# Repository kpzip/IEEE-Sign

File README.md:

# IEEE Sign

It's a sign that says "IEEE" using Argb lights. I don't know what more to say.

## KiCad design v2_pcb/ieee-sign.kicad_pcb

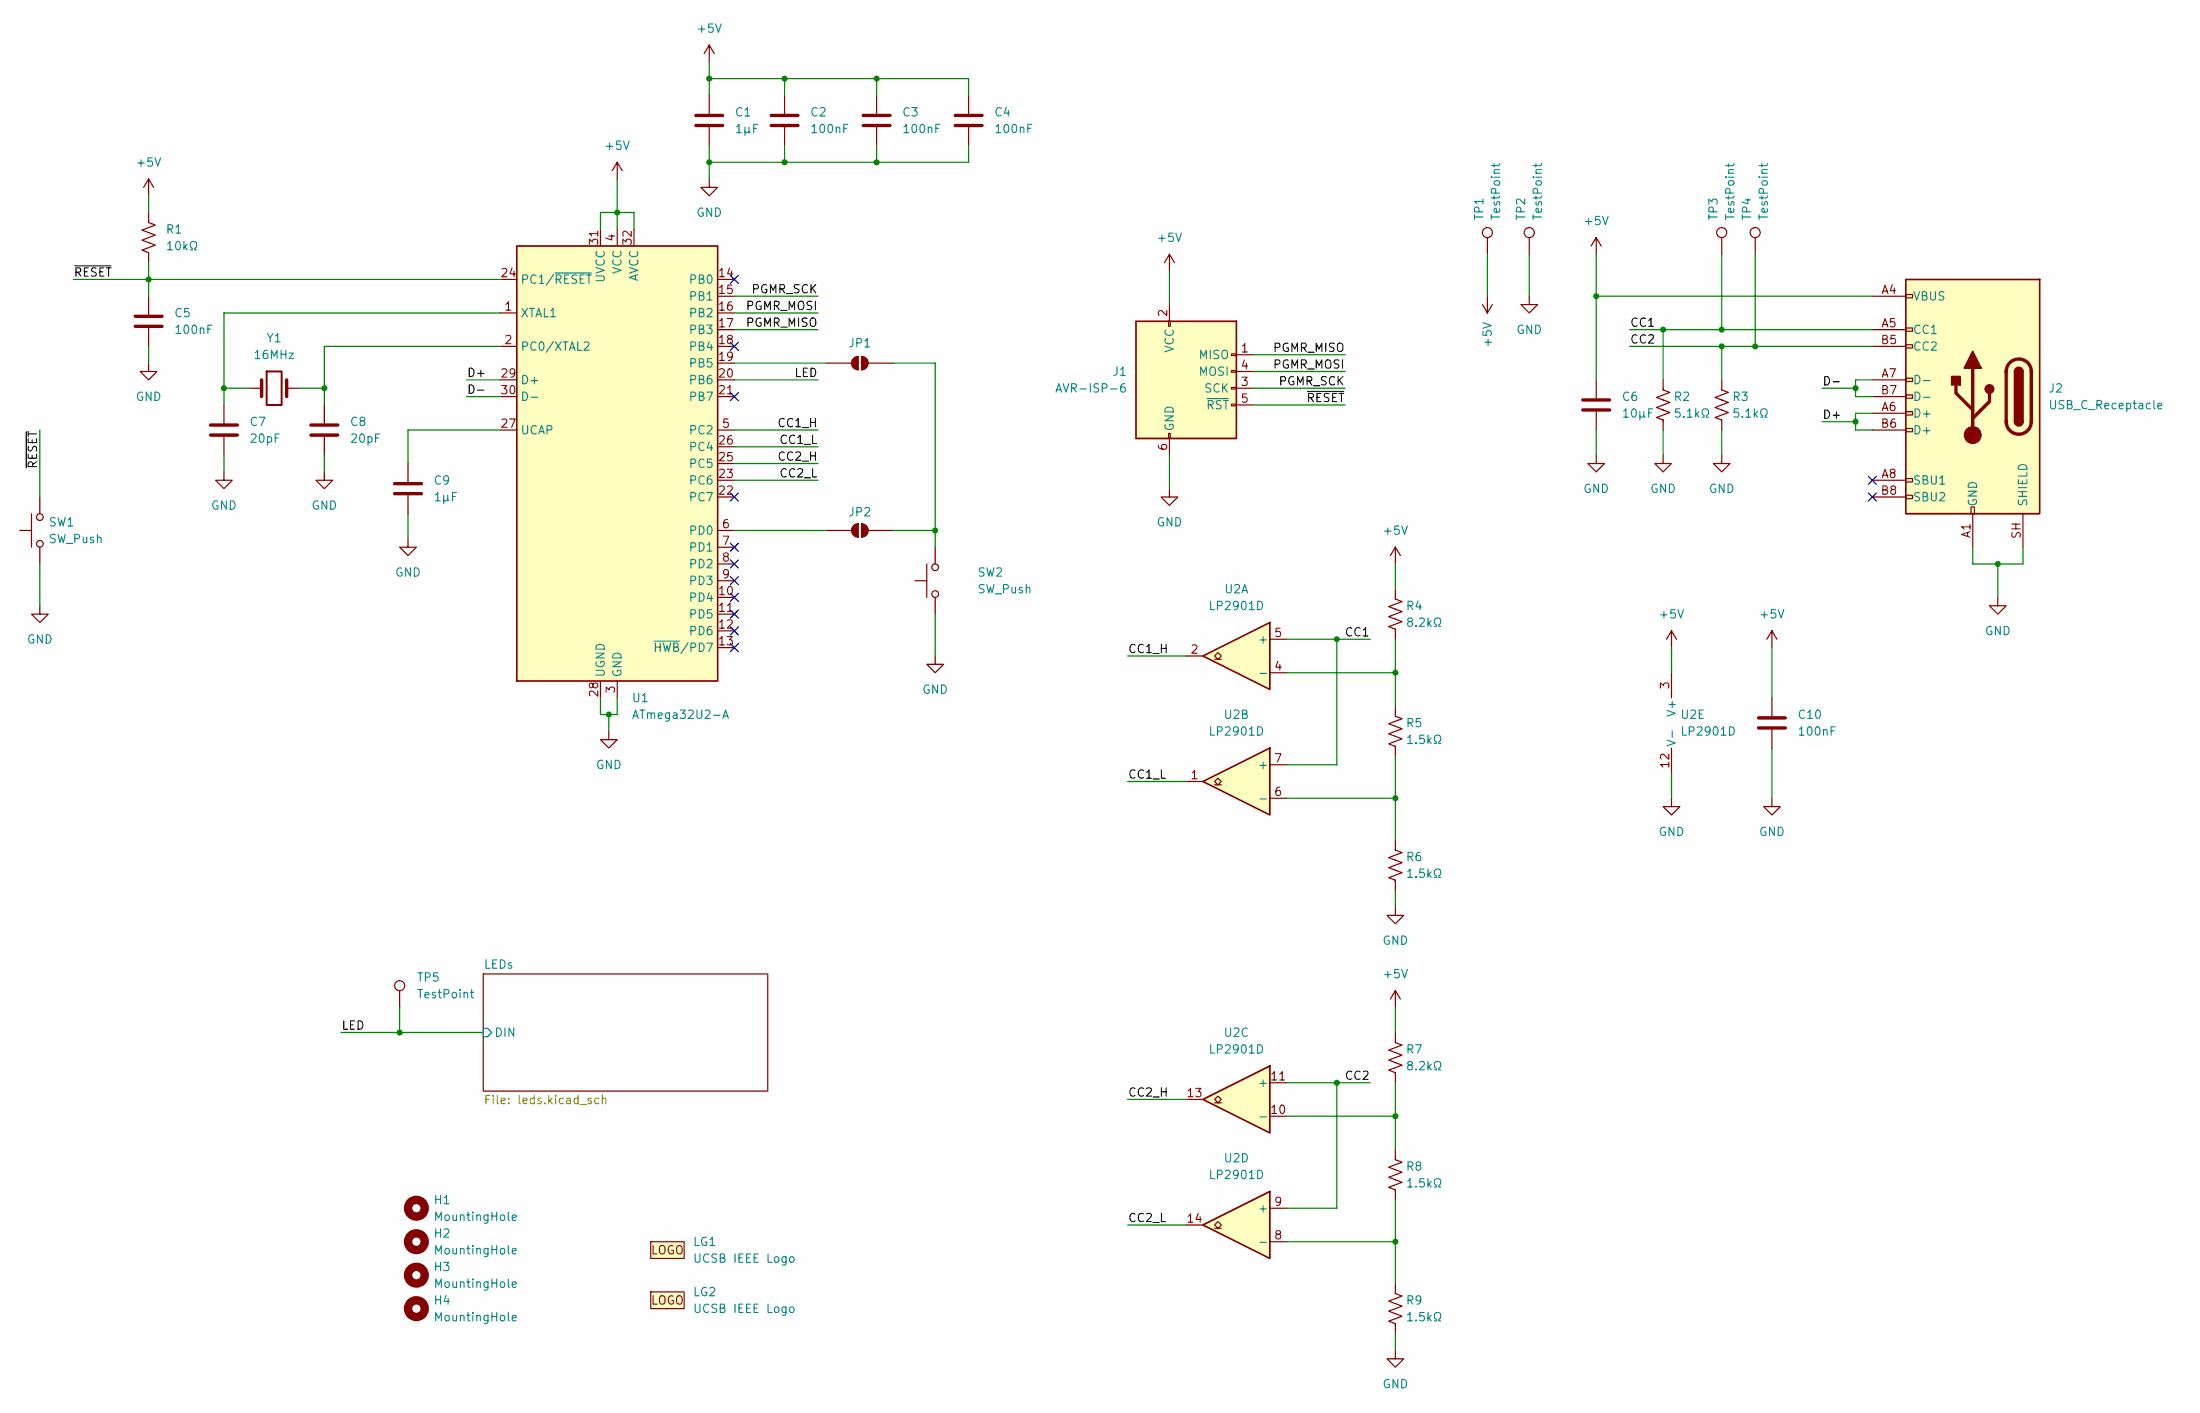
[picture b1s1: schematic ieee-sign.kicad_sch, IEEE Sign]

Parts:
C1, C9: 1μF; C_1206_3216Metric_Pad1.33x1.80mm_HandSolder; Manufacturer Part Number CL31B105KAHNNNE
C2, C3, C4, C5, C10: 100nF; C_1206_3216Metric_Pad1.33x1.80mm_HandSolder; Manufacturer Part Number C1206C104K5RACTU
C6: 10μF; C_1206_3216Metric_Pad1.33x1.80mm_HandSolder; Manufacturer Part Number CL31A106MAHNNNE
C7, C8: 20pF; C_0603_1608Metric_Pad1.08x0.95mm_HandSolder; Manufacturer Part Number C0603C200J5GACTU
H1, H2, H3, H4: MountingHole; MountingHole_3.2mm_M3
J1: AVR-ISP-6; IDC-Header_2x03_P2.54mm_Vertical; Manufacturer Part Number 61200621621
J2: USB_C_Receptacle; USB_C_Receptacle_GCT_USB4105-xx-A_16P_TopMnt_Horizontal; Manufacturer Part Number USB4105-GF-A
JP1, JP2: SolderJumper-2_P1.3mm_Open_RoundedPad1.0x1.5mm
LG1: UCSB IEEE Logo; UCSB_IEEE_Logo
LG2: UCSB IEEE Logo; UCSB_IEEE_Logo_Text
R1: 10kΩ; R_1206_3216Metric_Pad1.30x1.75mm_HandSolder; Manufacturer Part Number RMCF1206FT10K0
R2, R3: 5.1kΩ; R_1206_3216Metric_Pad1.30x1.75mm_HandSolder; Manufacturer Part Number RC1206FR-075K1L
R4, R7: 8.2kΩ; R_1206_3216Metric_Pad1.30x1.75mm_HandSolder; Manufacturer Part Number RC1206FR-078K2L
R5, R6, R8, R9: 1.5kΩ; R_1206_3216Metric_Pad1.30x1.75mm_HandSolder; Manufacturer Part Number RNCP1206FTD1K50
SW1, SW2: SW_Push; SW_PUSH_6mm; Manufacturer Part Number PTS645SL43-2 LFS
TP1, TP2, TP3, TP4, TP5: TestPoint; TestPoint_Pad_D1.0mm
U1: ATmega32U2-A; TQFP-32_7x7mm_P0.8mm; Manufacturer Part Number ATMEGA32U2-AUR
U2: LP2901D; SOIC-14_3.9x8.7mm_P1.27mm; Manufacturer Part Number LP2901D
Y1: 16MHz; Crystal_HC49-U_Vertical; Manufacturer Part Number 16M20P2/49US

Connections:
+5V: C1.1, C2.1, C3.1, C4.1, C6.1, C10.1, J1.2 (VCC), J2.A4 (VBUS), J2.A9 (VBUS), J2.B4 (VBUS), J2.B9 (VBUS), R1.1, R4.1, R7.1, TP1.1 (1_1), U1.4 (VCC), U1.31 (UVCC), U1.32 (AVCC), U2.3 (V+); also elsewhere on the board
/CC1: J2.A5 (CC1), R2.1, TP3.1 (1_1), U2.5 (+), U2.7 (+)
/CC1_H: U1.5 (PC2), U2.2
/CC1_L: U1.26 (PC4), U2.1
/CC2: J2.B5 (CC2), R3.1, TP4.1 (1_1), U2.9 (+), U2.11 (+)
/CC2_H: U1.25 (PC5), U2.13
/CC2_L: U1.23 (PC6), U2.14
/D+: J2.A6 (D+), J2.B6 (D+), U1.29 (D+)
/D-: J2.A7 (D-), J2.B7 (D-), U1.30 (D-)
/LED: TP5.1 (1_1), U1.20 (PB6); also elsewhere on the board
/PGMR_MISO: J1.1 (MISO), U1.17 (PB3)
/PGMR_MOSI: J1.4 (MOSI), U1.16 (PB2)
/PGMR_SCK: J1.3 (SCK), U1.15 (PB1)
/~RESET: C5.1, J1.5 (~RST), R1.2, SW1.2, U1.24 (PC1/~RESET)
GND: C1.2, C2.2, C3.2, C4.2, C5.2, C6.2, C7.2, C8.2, C9.2, C10.2, J1.6 (GND), J2.A1 (GND), J2.A12 (GND), J2.B1 (GND), J2.B12 (GND), J2.SH (SHIELD), R2.2, R3.2, R6.2, R9.2, SW1.1, SW2.1, TP2.1 (1_1), U1.3 (GND), U1.28 (UGND), U2.12 (V-); also elsewhere on the board
unnamed: JP1.1 (A), U1.19 (PB5)
unnamed: JP1.2 (B), JP2.2 (B), SW2.2
unnamed: JP2.1 (A), U1.6 (PD0)
unnamed: C8.1, U1.2 (PC0/XTAL2), Y1.2
unnamed: C9.1, U1.27 (UCAP)
unnamed: C7.1, U1.1 (XTAL1), Y1.1
unnamed: R4.2, R5.1, U2.4 (-)
unnamed: R5.2, R6.1, U2.6 (-)
unnamed: R7.2, R8.1, U2.10 (-)
unnamed: R8.2, R9.1, U2.8 (-)

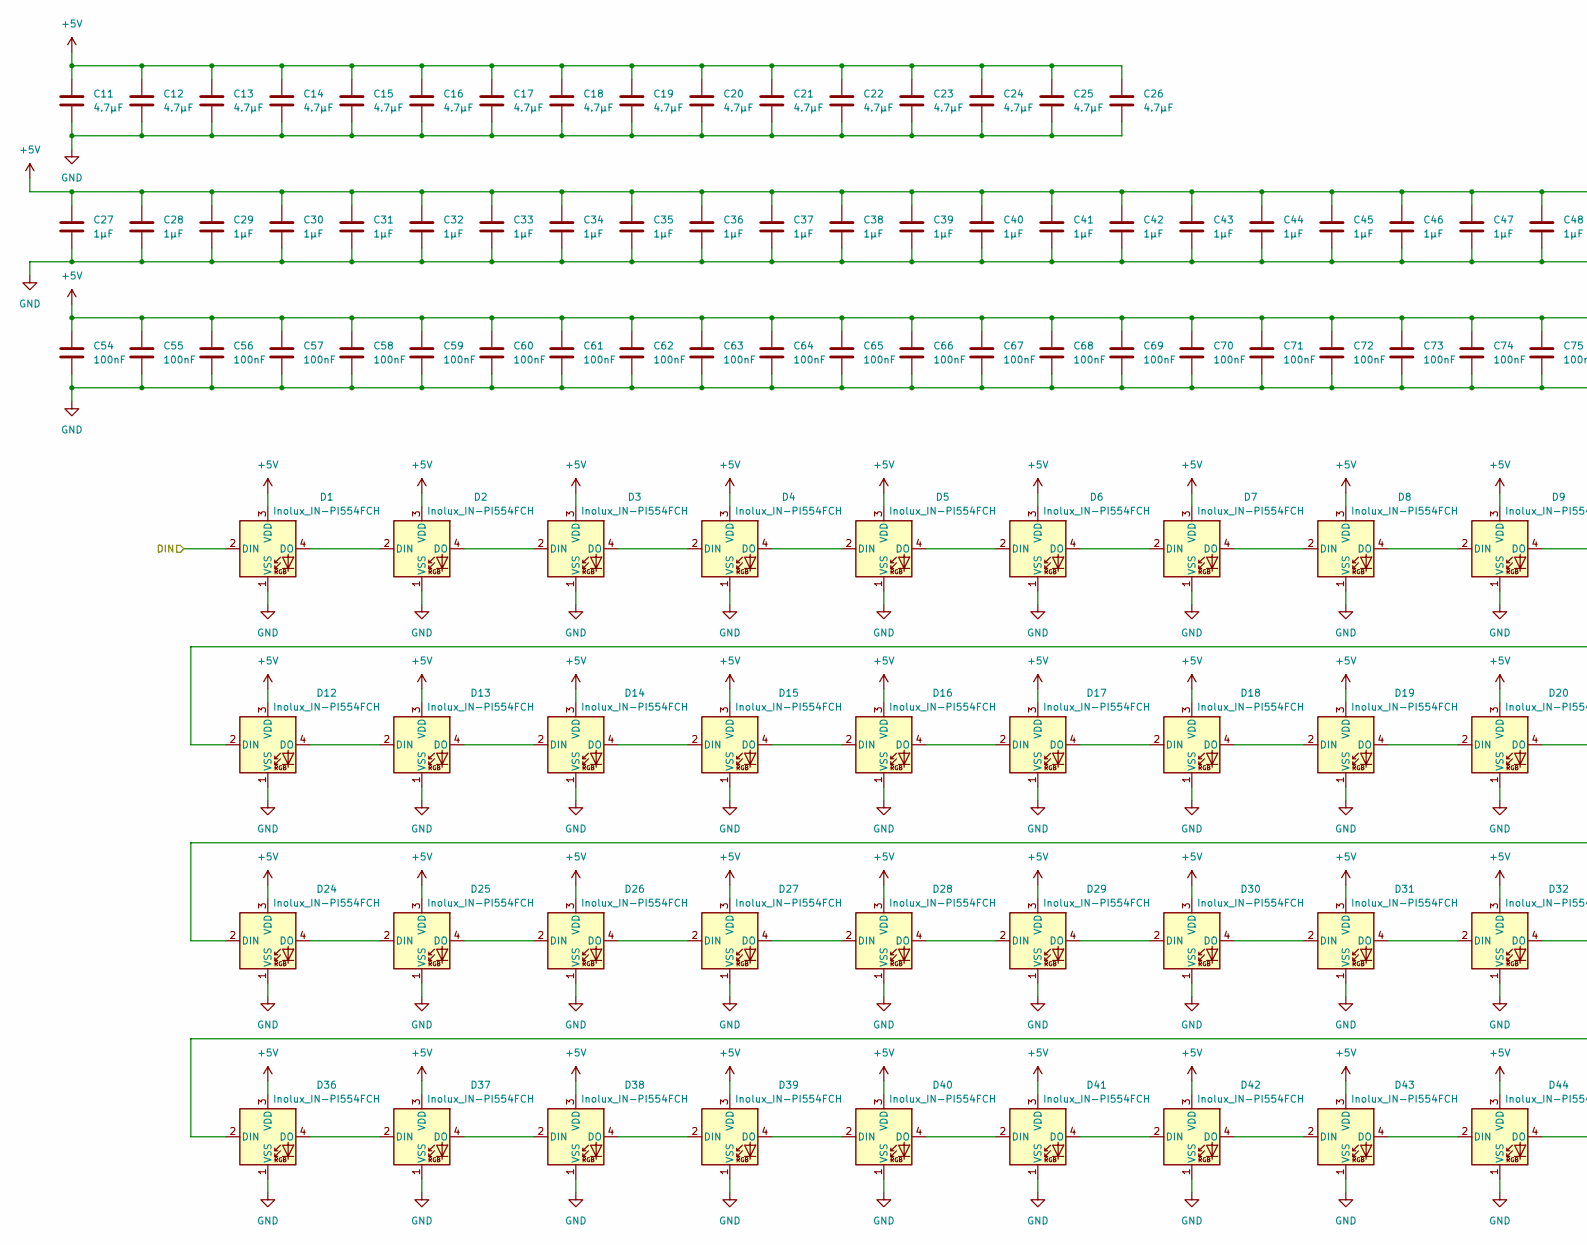
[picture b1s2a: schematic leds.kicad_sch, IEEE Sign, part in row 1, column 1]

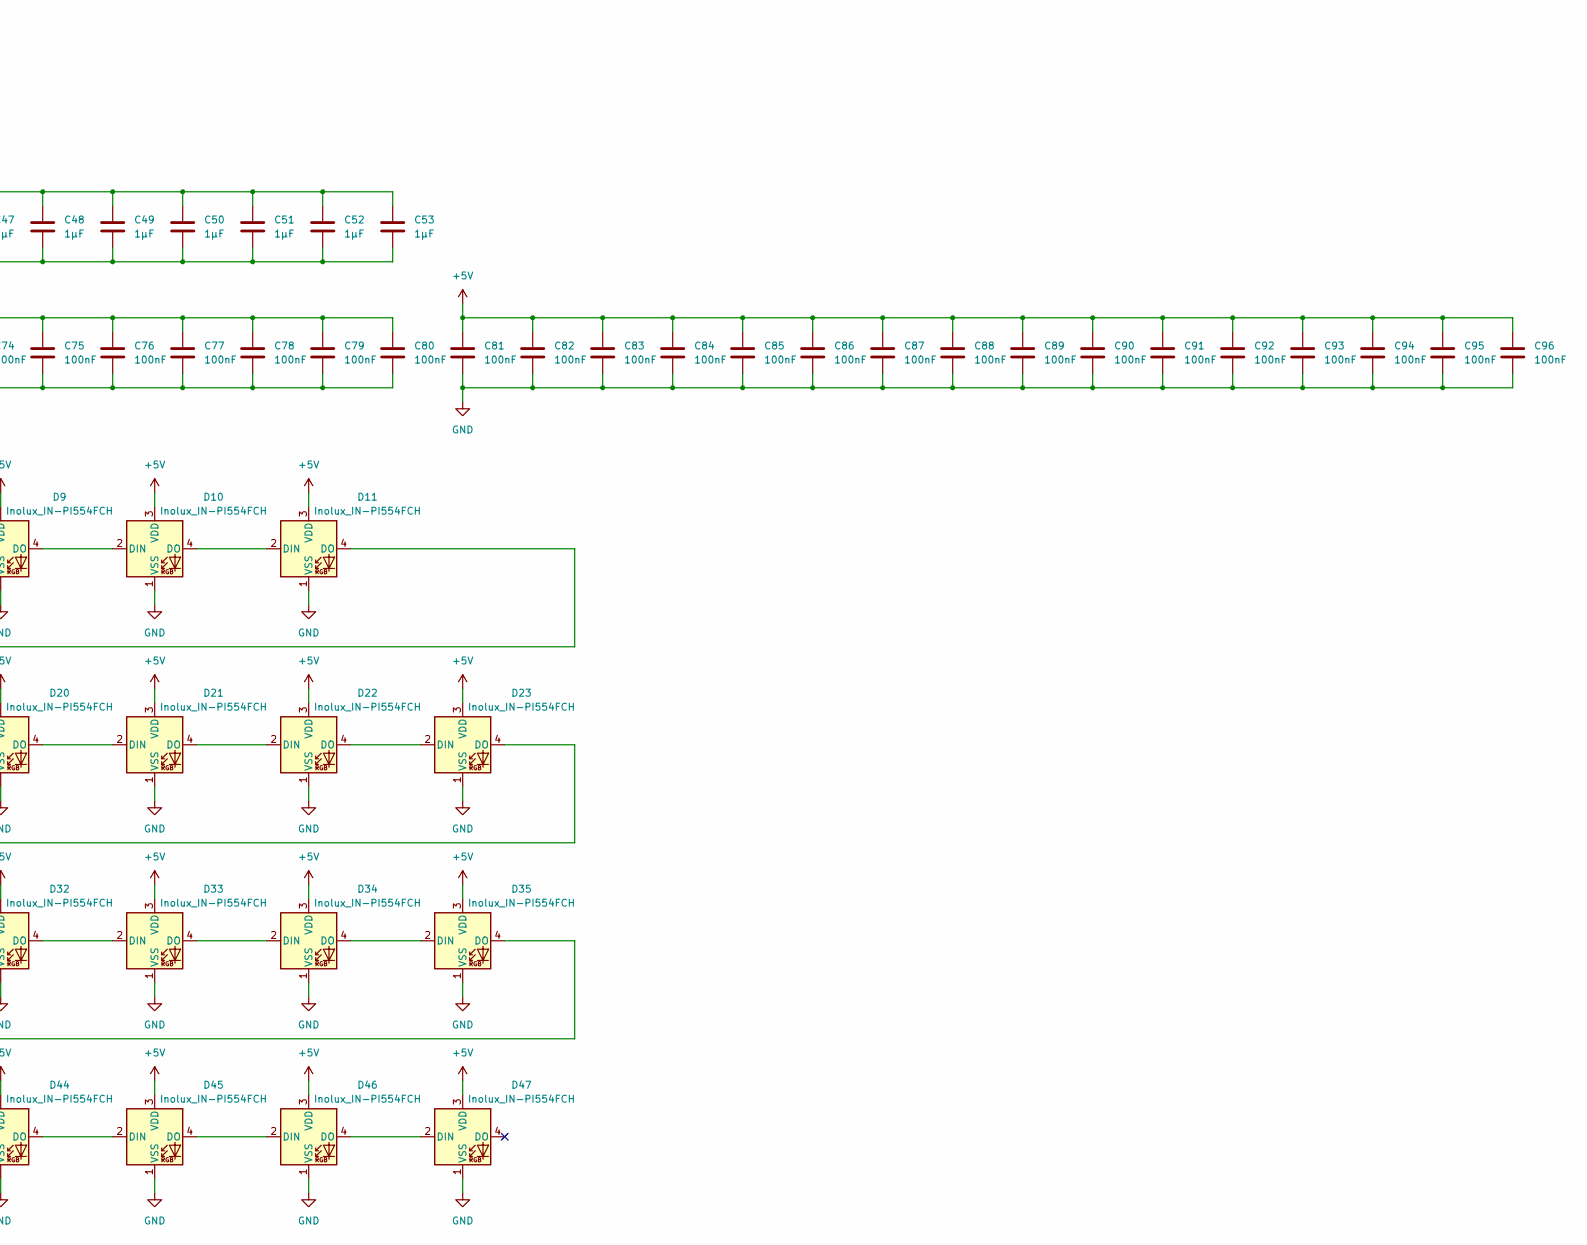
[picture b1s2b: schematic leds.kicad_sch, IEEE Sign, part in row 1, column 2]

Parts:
C11, C12, C13, C14, C15, C16, C17, C18, C19, C20, C21, C22, C23, C24, C25, C26: 4.7μF; C_1206_3216Metric_Pad1.33x1.80mm_HandSolder; Manufacturer Part Number CL31B475KAHNNNE
C27, C28, C29, C30, C31, C32, C33, C34, C35, C36, C37, C38, C39, C40, C41, C42, C43, C44, C45, C46, C47, C48, C49, C50, C51, C52, C53: 1μF; C_1206_3216Metric_Pad1.33x1.80mm_HandSolder; Manufacturer Part Number CL31B105KAHNNNE
C54, C55, C56, C57, C58, C59, C60, C61, C62, C63, C64, C65, C66, C67, C68, C69, C70, C71, C72, C73, C74, C75, C76, C77, C78, C79, C80, C81, C82, C83, C84, C85, C86, C87, C88, C89, C90, C91, C92, C93, C94, C95, C96: 100nF; C_1206_3216Metric_Pad1.33x1.80mm_HandSolder; Manufacturer Part Number C1206C104K5RACTU
D1, D2, D3, D4, D5, D6, D7, D8, D9, D10, D11, D12, D13, D14, D15, D16, D17, D18, D19, D20, D21, D22, D23, D24, D25, D26, D27, D28, D29, D30, D31, D32, D33, D34, D35, D36, D37, D38, D39, D40, D41, D42, D43, D44, D45, D46, D47: Inolux_IN-PI554FCH; LED_Inolux_IN-PI554FCH_PLCC4_5.0x5.0mm_P3.2mm; Manufacturer Part Number IN-PI554FCH

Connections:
+5V: C11.1, C12.1, C13.1, C14.1, C15.1, C16.1, C17.1, C18.1, C19.1, C20.1, C21.1, C22.1, C23.1, C24.1, C25.1, C26.1, C27.1, C28.1, C29.1, C30.1, C31.1, C32.1, C33.1, C34.1, C35.1, C36.1, C37.1, C38.1, C39.1, C40.1, C41.1, C42.1, C43.1, C44.1, C45.1, C46.1, C47.1, C48.1, C49.1, C50.1, C51.1, C52.1, C53.1, C54.1, C55.1, C56.1, C57.1, C58.1, C59.1, C60.1, C61.1, C62.1, C63.1, C64.1, C65.1, C66.1, C67.1, C68.1, C69.1, C70.1, C71.1, C72.1, C73.1, C74.1, C75.1, C76.1, C77.1, C78.1, C79.1, C80.1, C81.1, C82.1, C83.1, C84.1, C85.1, C86.1, C87.1, C88.1, C89.1, C90.1, C91.1, C92.1, C93.1, C94.1, C95.1, C96.1, D1.3 (VDD), D2.3 (VDD), D3.3 (VDD), D4.3 (VDD), D5.3 (VDD), D6.3 (VDD), D7.3 (VDD), D8.3 (VDD), D9.3 (VDD), D10.3 (VDD), D11.3 (VDD), D12.3 (VDD), D13.3 (VDD), D14.3 (VDD), D15.3 (VDD), D16.3 (VDD), D17.3 (VDD), D18.3 (VDD), D19.3 (VDD), D20.3 (VDD), D21.3 (VDD), D22.3 (VDD), D23.3 (VDD), D24.3 (VDD), D25.3 (VDD), D26.3 (VDD), D27.3 (VDD), D28.3 (VDD), D29.3 (VDD), D30.3 (VDD), D31.3 (VDD), D32.3 (VDD), D33.3 (VDD), D34.3 (VDD), D35.3 (VDD), D36.3 (VDD), D37.3 (VDD), D38.3 (VDD), D39.3 (VDD), D40.3 (VDD), D41.3 (VDD), D42.3 (VDD), D43.3 (VDD), D44.3 (VDD), D45.3 (VDD), D46.3 (VDD), D47.3 (VDD); also elsewhere on the board
/LED: D1.2 (DIN); also elsewhere on the board
GND: C11.2, C12.2, C13.2, C14.2, C15.2, C16.2, C17.2, C18.2, C19.2, C20.2, C21.2, C22.2, C23.2, C24.2, C25.2, C26.2, C27.2, C28.2, C29.2, C30.2, C31.2, C32.2, C33.2, C34.2, C35.2, C36.2, C37.2, C38.2, C39.2, C40.2, C41.2, C42.2, C43.2, C44.2, C45.2, C46.2, C47.2, C48.2, C49.2, C50.2, C51.2, C52.2, C53.2, C54.2, C55.2, C56.2, C57.2, C58.2, C59.2, C60.2, C61.2, C62.2, C63.2, C64.2, C65.2, C66.2, C67.2, C68.2, C69.2, C70.2, C71.2, C72.2, C73.2, C74.2, C75.2, C76.2, C77.2, C78.2, C79.2, C80.2, C81.2, C82.2, C83.2, C84.2, C85.2, C86.2, C87.2, C88.2, C89.2, C90.2, C91.2, C92.2, C93.2, C94.2, C95.2, C96.2, D1.1 (VSS), D2.1 (VSS), D3.1 (VSS), D4.1 (VSS), D5.1 (VSS), D6.1 (VSS), D7.1 (VSS), D8.1 (VSS), D9.1 (VSS), D10.1 (VSS), D11.1 (VSS), D12.1 (VSS), D13.1 (VSS), D14.1 (VSS), D15.1 (VSS), D16.1 (VSS), D17.1 (VSS), D18.1 (VSS), D19.1 (VSS), D20.1 (VSS), D21.1 (VSS), D22.1 (VSS), D23.1 (VSS), D24.1 (VSS), D25.1 (VSS), D26.1 (VSS), D27.1 (VSS), D28.1 (VSS), D29.1 (VSS), D30.1 (VSS), D31.1 (VSS), D32.1 (VSS), D33.1 (VSS), D34.1 (VSS), D35.1 (VSS), D36.1 (VSS), D37.1 (VSS), D38.1 (VSS), D39.1 (VSS), D40.1 (VSS), D41.1 (VSS), D42.1 (VSS), D43.1 (VSS), D44.1 (VSS), D45.1 (VSS), D46.1 (VSS), D47.1 (VSS); also elsewhere on the board
unnamed: D1.4 (DO), D2.2 (DIN)
unnamed: D2.4 (DO), D3.2 (DIN)
unnamed: D3.4 (DO), D4.2 (DIN)
unnamed: D4.4 (DO), D5.2 (DIN)
unnamed: D5.4 (DO), D6.2 (DIN)
unnamed: D6.4 (DO), D7.2 (DIN)
unnamed: D7.4 (DO), D8.2 (DIN)
unnamed: D8.4 (DO), D9.2 (DIN)
unnamed: D9.4 (DO), D10.2 (DIN)
unnamed: D10.4 (DO), D11.2 (DIN)
unnamed: D11.4 (DO), D12.2 (DIN)
unnamed: D12.4 (DO), D13.2 (DIN)
unnamed: D13.4 (DO), D14.2 (DIN)
unnamed: D14.4 (DO), D15.2 (DIN)
unnamed: D15.4 (DO), D16.2 (DIN)
unnamed: D16.4 (DO), D17.2 (DIN)
unnamed: D17.4 (DO), D18.2 (DIN)
unnamed: D18.4 (DO), D19.2 (DIN)
unnamed: D19.4 (DO), D20.2 (DIN)
unnamed: D20.4 (DO), D21.2 (DIN)
unnamed: D21.4 (DO), D22.2 (DIN)
unnamed: D22.4 (DO), D23.2 (DIN)
unnamed: D23.4 (DO), D24.2 (DIN)
unnamed: D24.4 (DO), D25.2 (DIN)
unnamed: D25.4 (DO), D26.2 (DIN)
unnamed: D26.4 (DO), D27.2 (DIN)
unnamed: D27.4 (DO), D28.2 (DIN)
unnamed: D28.4 (DO), D29.2 (DIN)
unnamed: D29.4 (DO), D30.2 (DIN)
unnamed: D30.4 (DO), D31.2 (DIN)
unnamed: D31.4 (DO), D32.2 (DIN)
unnamed: D32.4 (DO), D33.2 (DIN)
unnamed: D33.4 (DO), D34.2 (DIN)
unnamed: D34.4 (DO), D35.2 (DIN)
unnamed: D35.4 (DO), D36.2 (DIN)
unnamed: D36.4 (DO), D37.2 (DIN)
unnamed: D37.4 (DO), D38.2 (DIN)
unnamed: D38.4 (DO), D39.2 (DIN)
unnamed: D39.4 (DO), D40.2 (DIN)
unnamed: D40.4 (DO), D41.2 (DIN)
unnamed: D41.4 (DO), D42.2 (DIN)
unnamed: D42.4 (DO), D43.2 (DIN)
unnamed: D43.4 (DO), D44.2 (DIN)
unnamed: D44.4 (DO), D45.2 (DIN)
unnamed: D45.4 (DO), D46.2 (DIN)
unnamed: D46.4 (DO), D47.2 (DIN)

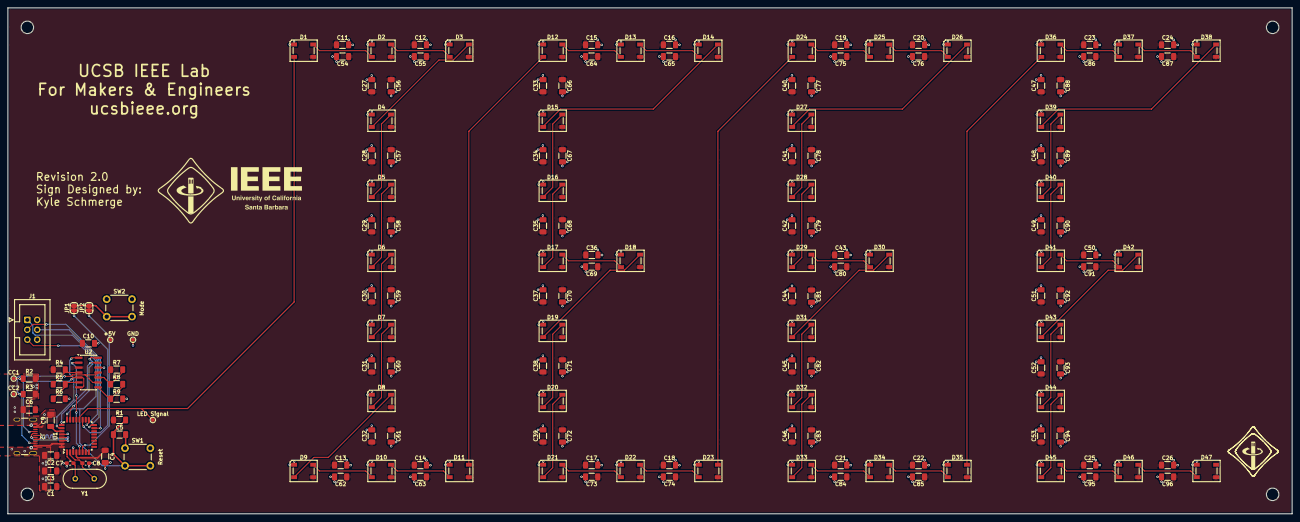
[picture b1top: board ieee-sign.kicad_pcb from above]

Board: 2 copper layers, 330.0 x 130.0 mm, 172 parts (0 on the bottom side), 71 nets.

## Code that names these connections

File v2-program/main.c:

/*
 * main.c
 *
 * Created: 11/21/2024 11:37:21 PM
 * Author : Kyle Schmerge, Daniel Van Dalsem
 */ 

#define F_CPU 16000000UL

#include <avr/io.h>
#include <avr/interrupt.h>
#include <util/delay.h>

#include <stdint.h>
#include <string.h>
#include <stdbool.h>
#include <math.h>

// For setting individual bits
#define sbi(x,b) (x) |= 1<<(b)
#define cbi(x,b) (x) &= ~(1<<(b))

#define LED_PIN 6
#define SWITCH_PIN PCINT5
#define STRIP_LEN 47
#define NUM_PROGRAMS 6

#define TCC0 0
#define TCC1 1

#define DEBOUNCE_TIME_MS 25UL

// Order is important! colors are sent as g, r, b
typedef struct Color {
	unsigned char g;
	unsigned char r;
	unsigned char b;
} Color;

Color hsv2rgb(float, float, float);

typedef struct xorshift32_state {
	uint32_t a;
} xorshift32_state;

const Color red = { .r = 128, .g = 0, .b = 0 };
const Color white = { .r = 128, .g = 128, .b = 128 };
const Color gold = { .r = 255, .g = 255, .b = 0 };
const Color green = { .r = 0, .g = 255, .b = 0 };
const Color lush_green = { .r = 50, .g = 168, .b = 82 };
const Color off = { .r = 0, .g = 0, .b = 0 };

static Color strip[STRIP_LEN];
static bool candy_state[STRIP_LEN] = { false };
static volatile int program = 0;

static volatile uint32_t millis;

/* The state must be initialized to non-zero */
static xorshift32_state randomstate = { .a = 0x75AE3D9A };

extern void output_grb(uint8_t * ptr, uint16_t count);
extern void reset();

#define DEBOUNCE_DELAY 100

#define SATURATION 100.0f
#define INTENSITY 100.0f

Color rainbow[STRIP_LEN];

uint32_t xorshift32() {
	/* Algorithm "xor" from p. 4 of Marsaglia, "Xorshift RNGs" */
	uint32_t x = randomstate.a;
	x ^= x << 13;
	x ^= x >> 17;
	x ^= x << 5;
	return randomstate.a = x;
}

bool randbool() {
	return xorshift32() % 2 == 0;
}

void setup() {
	// Set LED Pin as output
	sbi(DDRB, LED_PIN);
	cbi(PORTB, LED_PIN);
	// Set inputs for detecting usb power mode
	DDRC &= ~(1 << PC2);
	DDRC &= ~(1 << PC4);
	DDRC &= ~(1 << PC5);
	DDRC &= ~(1 << PC6);
	// cbi(DDRD, TCC0);
	// cbi(DDRD, TCC1);
	// cbi(PORTD, TCC0);
	// cbi(PORTD, TCC1);
	
	// Pin change interrupt on mode button
	// PCMSK0 = (1 << SWITCH_PIN);
	// PCICR = (1 << PCIE0);
	
	// Set program change switch pin as input and engage pull-up resistor
	// cbi(DDRB, SWITCH_PIN);
	// sbi(PORTB, SWITCH_PIN);
	DDRD &= ~(1 << DDD0);  // Set PD0 as Input
    PORTD |= (1 << PORTD0);  // Enable internal pull-up resistor
	EICRA |= (1 << ISC01);
    EICRA &= ~(1 << ISC00);
	// Writing the sense-control bits above can set INTF0; clear it so we
	// don't service a phantom "button press" the instant sei() runs.
	EIFR |= (1 << INTF0);
	EIMSK |= (1 << INT0);

	
	// 1kHz millis interrupt
	TCCR0A = (1 << WGM01);
	OCR0A = 249;
	TCCR0B = (1 << CS01) | (1 << CS00);
	TIMSK0 = (1 << OCIE0A);
	
	// Precompute rainbow
	for(int i = 0; i < STRIP_LEN; i++)
		rainbow[i] = hsv2rgb(360.0f * (STRIP_LEN - i - 1) / STRIP_LEN, SATURATION, INTENSITY);
	
	for (int i = 0; i < STRIP_LEN - 1; i++) {
		candy_state[i] = randbool();
	}
	
	sei();
	
}

ISR(TIMER0_COMPA_vect) {
	millis++;
}

ISR(INT0_vect) {
    _delay_ms(DEBOUNCE_TIME_MS);

    if (bit_is_clear(PIND, PIND0)) {
		program += 1;
		// if (program > 6) {
		// 	program = 0;
		// }
    }
    
    EIFR |= (1 << INTF0);
}

// ISR(PCINT0_vect) {
// 	static uint32_t last_change = 0;
// 	if(!(PINB & (1 << SWITCH_PIN)) && millis - last_change > DEBOUNCE_DELAY)
// 		program++;
// 	last_change = millis;
// }

Color hsv2rgb(float H, float S, float V) {
	float r = 0, g = 0, b = 0;
	
	float h = H / 360;
	float s = S / 100;
	float v = V / 100;
	
	int i = floor(h * 6);
	float f = h * 6 - i;
	float p = v * (1 - s);
	float q = v * (1 - f * s);
	float t = v * (1 - (1 - f) * s);
	
	switch (i % 6) {
		case 0: r = v, g = t, b = p; break;
		case 1: r = q, g = v, b = p; break;
		case 2: r = p, g = v, b = t; break;
		case 3: r = p, g = q, b = v; break;
		case 4: r = t, g = p, b = v; break;
		case 5: r = v, g = p, b = q; break;
	}
	
	Color color;
	color.r = r * 255;
	color.g = g * 255;
	color.b = b * 255;
	
	return color;
}

void show(Color * colors, int colors_len) {
	output_grb((uint8_t*) colors, colors_len * sizeof(Color));
	reset();
}

void set_solid(Color c, Color * colors, int colors_len) {
	for (int i = 0; i < colors_len; i++) {
		colors[i] = c;
	}
}

void candy_cane() {
	// strip[STRIP_LEN - 1] = gold;
	for (int i = 0; i < STRIP_LEN; i++) {
		strip[i] = randbool() ? red : white;
	}
	show(strip, STRIP_LEN);
	_delay_ms(500);
}

void candy_cane2() {
	int flip = xorshift32() % STRIP_LEN;
	candy_state[flip] = !candy_state[flip];
	for (int i = 0; i < STRIP_LEN; i++) {
		strip[i] = candy_state[i] ? red : white;
	}
	show(strip, STRIP_LEN);
	_delay_ms(500);
}

void solid_green() {
	// strip[STRIP_LEN - 1] = gold;
	set_solid(green, strip, STRIP_LEN);
	show(strip, STRIP_LEN);
	_delay_ms(250);
}

void solid_white() {
	// strip[STRIP_LEN - 1] = gold;
	set_solid(white, strip, STRIP_LEN);
	show(strip, STRIP_LEN);
	_delay_ms(250);
}

static int white_wave_state = 0;

#define STAR_NUM_BLINKS 3

void white_wave() {
	for (int i = 0; i < STRIP_LEN; i++) {
		if (i == (STRIP_LEN - 1) && white_wave_state >= (STRIP_LEN - 1)) {
			strip[i] = white_wave_state % 2 == 0 ? off : gold;
		}
		else if (i == white_wave_state) {
			strip[i] = white;
		}
		else {
			strip[i] = off;
		}
	}
	show(strip, STRIP_LEN);
	_delay_ms(250);
	white_wave_state++;
	white_wave_state %= (STRIP_LEN + STAR_NUM_BLINKS * 2 - 1);
}

static bool green_red_state = false;

void green_red() {
	// strip[STRIP_LEN - 1] = gold;
	for (int i = 0; i < STRIP_LEN; i++) {
		if ((i + green_red_state) % 2 == 0) {
			strip[i] = green;
		}
		else {
			strip[i] = red;
		}
	}
	show(strip, STRIP_LEN);
	_delay_ms(250);
	green_red_state = !green_red_state;
}

const Color dark = { .r = 10, .g = 10, .b = 10 };

void low_brightness() {
	for (int i = 0; i < STRIP_LEN; i++) {
		strip[i] = dark;
	}
	show(strip, STRIP_LEN);
	_delay_ms(250);
}

void all_off() {
	for (int i = 0; i < STRIP_LEN; i++) {
		strip[i] = off;
	}
	show(strip, STRIP_LEN);
	_delay_ms(250);
}

static float hue_val = 0.0;

void rgb() {
	//strip[STRIP_LEN - 1] = gold;
	Color c = hsv2rgb(hue_val, SATURATION, INTENSITY);
	for (int i = 0; i < STRIP_LEN; i++) {
		strip[i] = c;
	}
	show(strip, STRIP_LEN);
	_delay_ms(25);
	hue_val += 1;
	hue_val = fmod(hue_val, 360);
}

void cycle() {
	for(int i = 0; i < STRIP_LEN; i++)
		strip[i] = hsv2rgb(360 - fmod(hue_val + 360.0f * i / STRIP_LEN, 360), SATURATION, INTENSITY);
	show(strip, STRIP_LEN);
	_delay_ms(10);
	hue_val += 10;
	hue_val = fmod(hue_val, 360);
}

void bugged_but_cool_cycle() {
	static float fade_pos = 0;

	for(int i = 0; i < STRIP_LEN; i++) {
		float pos = (float)i / STRIP_LEN;
		float arg = (fade_pos - 2 * (pos - 0.5f));
		strip[i] = hsv2rgb(fmod(hue_val + 360.0f * pos, 360), SATURATION, 100 * powf(0.5 * (sin(arg * 2 * M_PI) + 1), 5));
	}
	show(strip, STRIP_LEN);
	_delay_ms(10);
	
	hue_val += 10;
	hue_val = fmod(hue_val, 360);
	
	fade_pos += 0.01;
	if(fade_pos > 1)
		fade_pos = 0;
}

void death() {
	static int offset = 0;
	static char doom = 0;
	
	offset = xorshift32() % STRIP_LEN;
	
	if(doom) {
		for(int i = 0; i < STRIP_LEN; i++) {
			int ind = (offset + i) % STRIP_LEN;
			strip[i] = rainbow[ind];
		}
		offset = (offset + 1) % STRIP_LEN;
		doom = 0;
	} else {
		for(int i = 0; i < STRIP_LEN; i++) {
			strip[i].r = 0;
			strip[i].g = 0;
			strip[i].b = 0;
		}
		doom = 1;
	}
	
	show(strip, STRIP_LEN);
	
	_delay_ms(25);
}

void err() {
	// Turn all LEDs off if the USB port cannot provide adequate power
	memset(strip, 0, sizeof(Color) * STRIP_LEN);
	strip[0] = red;
	show(strip, STRIP_LEN);
	_delay_ms(25);
}

int main(void) {
	
	// Initialize IO
	setup();
	
	// Set colors to all zero
	memset(strip, 0, sizeof(Color) * STRIP_LEN);
	
	while (1) {
		if ((PINC & (1 << PC4)) || (PINC & (1 << PC6)) || 1) {
			switch(program) {
				case 0:
					cycle();
					break;

				case 1:
					rgb();
					break;

				case 2:
					bugged_but_cool_cycle();
					break;

				case 3:
					death();
					break;

				case 4:
					candy_cane2();
					break;

				case 5:
					candy_cane();
					break;

				case 6:
					green_red();
					break;
				
				case 7:
					solid_green();
					break;

				case 8:
					solid_white();
					break;

				case 9:
					low_brightness();
					break;

				case 10:
					all_off();
					break;

				default:
					program = 0;
					break;
			}
		} else {
			err();
		}
	}
}

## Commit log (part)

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2025-05-27 stuff
2025-05-27 pcb files
2026-04-22 init
2026-04-22 schematic
2026-04-23 work
